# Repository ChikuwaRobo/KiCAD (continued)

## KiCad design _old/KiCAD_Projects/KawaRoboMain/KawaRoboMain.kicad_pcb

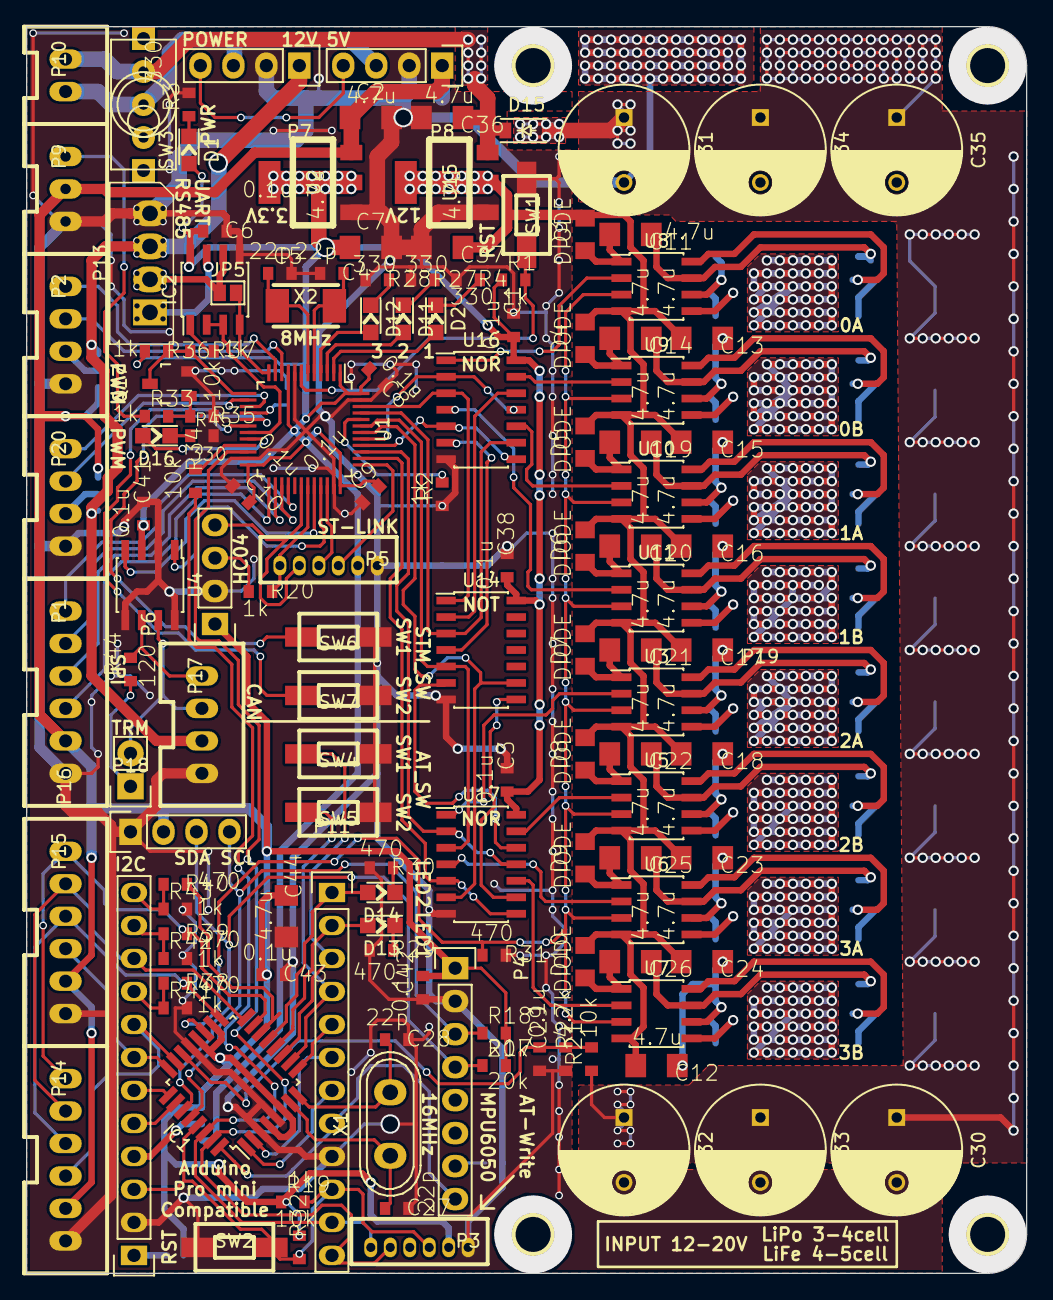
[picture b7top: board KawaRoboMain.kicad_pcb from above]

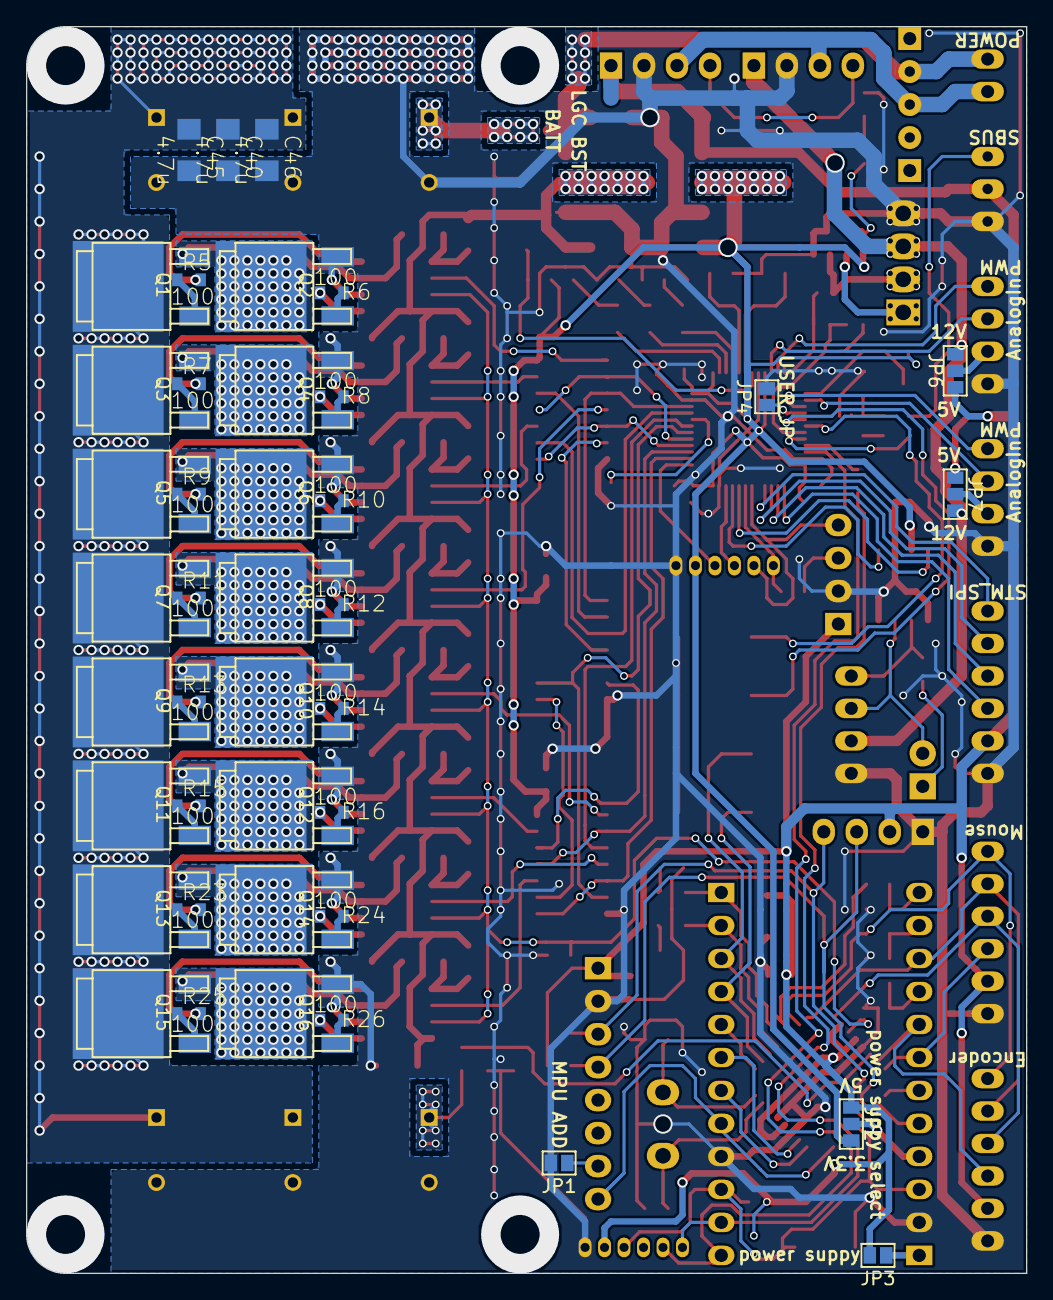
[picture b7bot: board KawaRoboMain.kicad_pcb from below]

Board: 2 copper layers, 77.0 x 96.0 mm, 178 parts (42 on the bottom side), 155 nets.

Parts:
C1, C3, C6, C8, C9, C10, C29, C38, C41, C42, C43: 0.1u; C1608_WP
C2, C7, C11, C12, C13, C14, C15, C16, C17, C18, C19, C20, C21, C22, C23, C24, C25, C26, C36, C37, C40, C44, C45, C46: 4.7u; C3216
C4, C5, C27, C28: 22p; C1608_WP
C30, C31, C32, C33, C34, C35: 220u; C_Radial_D10_L13_P5
D1, D2, D11, D12, D13, D14, D16: LED; LED_0805
D3, D4, D5, D6, D7, D8, D9, D10: DIODE; C2012
D15: DIODE; SOD-123
IC1: ATMEGA328P-A; TQFP-32_7x7mm_Pitch0.8mm
IC2: SP3485CN; SOIC-8_3.9x4.9mm_Pitch1.27mm
JP1, JP3, JP4, JP5: JUMPER; GS2
JP2, JP6, JP7: JUMPER3; GS3
P1, P14, P15: CONN_01X06; XA_6T
P2, P17, P20: CONN_01X04; XA_4T
P3, P5: CONN_01X06; ZH_6T
P4: CONN_01X08; Socket_Strip_Straight_1x08
P6, P7, P8, P18: CONN_01X04; Socket_Strip_Straight_1x04
P9: CONN_01X03; XA_3T
P10: CONN_01X02; XA_2T
P11, P12: CONN_01X12; Pin_Header_Straight_1x12
P13: CONN_01X04; Molex_SPOX-5267_22-03-5045_04x2.54mm_Straight
P16: CONN_01X02; Socket_Strip_Straight_1x02
P19: CONN_01X01; KawaRobo_Headsink
P21: CONN_01X01; kw
P22: CONN_01X01; ckw
Q1, Q2, Q3, Q4, Q5, Q6, Q7, Q8, Q9, Q10, Q11, Q12, Q13, Q14, Q15, Q16: MOSFET_N; SOT-428_GDS_compact
Q17: MOSFET_N; SOT-23_Handsoldering
R1, R2, R19, R20, R33, R36, R37, R41, R42, R43: 1k; C1608_WP
R3, R4, R27, R28, R45: 330; C1608_WP
R5, R6, R7, R8, R9, R10, R11, R12, R13, R14, R15, R16, R23, R24, R25, R26: 100; C1608_WP
R17, R18: 20k; C1608_WP
R21, R32, R34, R35: 10k; C1608_WP
R22: 4.7k; C1608_WP
R29, R30, R31, R38, R39, R40: 470; C1608_WP
R44: 120; C1608_WP
SW1, SW2, SW4, SW5, SW6, SW7: SW_PUSH; RP_SMD_Button
SW3: SWITCH_INV; SW_toggle_3P
U1: STM32F103_48; LQFP-48_7x7mm_Pitch0.5mm
U2: NCP1117ST33T3G; SOT-223_reg
U3, U5, U6, U7, U8, U9, U10, U11: NCP5359; SOIC-8_3.9x4.9mm_Pitch1.27mm
U4: MAX3051; SOIC-8_3.9x4.9mm_Pitch1.27mm
U14: 74HC04; SOIC-14_3.9x8.7mm_Pitch1.27mm
U15: NCP1117ST12T3G; SOT-223_reg
U16, U17: 74HC02; SOIC-14_3.9x8.7mm_Pitch1.27mm
X1: CRYSTAL; Crystal_HC50-U_Vertical
X2: CRYSTAL; ABM3_2pads

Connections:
+3.3V: C1.2, C3.2, C6.2, C7.1, C8.2, C9.2, C10.2, C38.2, C41.2, D1.1, IC2.8, JP2.3, P5.2, R1.1, R36.2, U1.1, U1.9, U1.24, U1.36, U1.48, U2.2, U4.3, U14.14, U16.14, U17.14
+5V: C2.1, C42.2, C43.2, C44.1, IC1.4, IC1.6, IC1.18, IC1.20, JP2.1, JP3.2, JP6.1, JP7.1, P1.2, P3.2, P4.1, P6.1, P8.1, P9.2, P14.2, P15.2, P18.2, R17.2, R18.2, R19.1, R32.1, U2.3
+12V: JP6.3, JP7.3, P7.1, P13.3, P17.2
+BATT: C30.1, C31.1, C32.1, C33.1, C34.1, C35.1, C40.1, C45.1, C46.1, D15.2, Q1.D, Q3.D, Q5.D, Q7.D, Q9.D, Q11.D, Q13.D, Q15.D, R21.1
/AT_A2: IC1.25, P12.6
/AT_A3: IC1.26, P12.5
/AT_LED1: D13.1, IC1.12, P11.2
/AT_LED2: D14.1, IC1.13, P11.1
/AT_RST: IC1.29, P3.3, P11.10, P12.3, R19.2, R32.2, SW2.2
/AT_RX: IC1.30, P3.6, P11.11, R34.2
/AT_SW1: IC1.11, P11.3, SW4.2
/AT_SW2: IC1.10, P11.4, SW5.2
/AT_TX: IC1.31, P3.5, P11.12, U1.22
/BOOT0: R2.2, U1.44
/CAN_RX: U1.32, U4.4
/CAN_TX: U1.33, U4.1
/DCDC_EN: P7.4, P8.4
/GD_12V: C12.2, C13.2, C15.2, C16.2, C17.2, C18.2, C23.2, C24.2, C37.1, D3.2, D4.2, D5.2, D6.2, D7.2, D8.2, D9.2, D10.2, U3.4, U5.4, U6.4, U7.4, U8.4, U9.4, U10.4, U11.4, U15.2
/I2C_SCL: IC1.28, P4.3, P18.4, R18.1
/I2C_SDA: IC1.27, P4.4, P18.3, R17.1
/INT0: IC1.32, P4.8, P11.8
/INT1: IC1.1, P11.7
/LOGIC_BATT: C36.1, D15.1, P10.2, SW3.1, U15.3
/Motor0CW: U1.41, U16.2, U16.11
/Motor0PWM: U1.46, U14.1, U16.3
/Motor1CW: U1.40, U16.5, U16.8
/Motor1PWM: U1.45, U14.3, U16.9
/Motor2CW: U1.39, U17.2, U17.11
/Motor2PWM: U1.43, U14.5, U17.3
/Motor3CW: U1.38, U17.5, U17.8
/Motor3PWM: U1.42, U14.9, U17.6
/Motor~SD: IC1.19, R31.2, U3.3, U5.3, U6.3, U7.3, U8.3, U9.3, U10.3, U11.3
/NRST: R1.2, SW1.2, U1.7
/OSC_IN: C4.1, U1.5, X2.1
/OSC_OUT: C5.1, U1.6, X2.2
/OUT_0_A: C11.1, Q1.S, Q2.D, U8.7
/OUT_0_B: C14.1, Q3.S, Q4.D, U9.7
/OUT_1_A: C19.1, Q5.S, Q6.D, U10.7
/OUT_1_B: C20.1, Q7.S, Q8.D, U11.7
/OUT_2_A: C21.1, Q9.S, Q10.D, U3.7
/OUT_2_B: C22.1, Q11.S, Q12.D, U5.7
/OUT_3_A: C25.1, Q13.S, Q14.D, U6.7
/OUT_3_B: C26.1, Q15.S, Q16.D, U7.7
/PWM_0_A: U8.2, U16.1
/PWM_0_B: U9.2, U16.13
/PWM_1_A: U10.2, U16.10
/PWM_1_B: U11.2, U16.4
/PWM_2_A: U3.2, U17.1
/PWM_2_B: U5.2, U17.13
/PWM_3_A: U6.2, U17.4
/PWM_3_B: U7.2, U17.10
/PWM_T2C1: P2.3, U1.10
/PWM_T2C2: P2.4, U1.11
/PWM_T3C1: P20.3, U1.14
/PWM_T3C2: P20.4, U1.15
/RAW: JP3.1, P12.1
/SBUS: P9.3, R33.1
/SERVO_DIR: IC2.2, IC2.3, U1.19
/SERVO_RX: Q17.D, R36.1, R37.2, U1.13
/SERVO_TX: IC2.4, JP5.2, U1.12
/SPI_MISO: IC1.16, P12.10, P14.5, P15.5
/SPI_MOSI: IC1.15, P14.6, P15.6, R39.1
/SPI_SCK: IC1.17, P14.4, P15.4, R38.1
/SPI_SS_ENC: IC1.23, P12.8, P14.3
/SPI_SS_Mouse: IC1.24, P12.7, P15.3
/SPI_SS_USB: IC1.14, R40.1
/STM_LED1: D2.1, U1.2
/STM_LED2: D11.1, U1.3
/STM_LED3: D12.1, U1.4
/STM_LED4: D16.1, U1.20
/STM_MISO: P1.5, U1.27
/STM_MOSI: P1.6, U1.28
/STM_SCK: P1.4, U1.26
/STM_SW1: SW6.2, U1.18
/STM_SW2: SW7.2, U1.17
/STM_~SS0: P1.3, U1.25
/SWCLK: P5.3, U1.37
/SWDIO: P5.4, U1.34
/USART_RX: P5.6, R20.1, U1.31
/USART_TX: P5.5, P6.4, U1.30
/VALVE_0: IC1.2, P11.6
/VALVE_1: IC1.9, P11.5
/batt_voltage: C29.1, IC1.22, R21.2, R22.1
GND: C1.1, C2.2, C3.1, C4.2, C5.2, C6.1, C7.2, C8.1, C9.1, C10.1, C12.1, C13.1, C15.1, C16.1, C17.1, C18.1, C23.1, C24.1, C27.1, C28.1, C29.2, C30.2, C31.2, C32.2, C33.2, C34.2, C35.2, C36.2, C37.2, C38.1, C40.2, C41.1, C42.1, C43.1, C44.2, C45.2, C46.2, IC1.3, IC1.5, IC1.21, IC2.5, JP1.2, JP4.2, P1.1, P2.1, P3.1, P4.2, P5.1, P6.2, P7.2, P8.2, P9.1, P11.9, P12.2, P13.4, P14.1, P15.1, P17.1, P18.1, P20.1, Q2.S, Q4.S, Q6.S, Q8.S, Q10.S, Q12.S, Q14.S, Q16.S, Q17.S, R2.1, R3.2, R4.2, R22.2, R27.2, R28.2, R29.2, R30.2, R31.1, R35.1, R41.2, R42.2, R43.2, R45.2, SW1.1, SW2.1, SW4.1, SW5.1, SW6.1, SW7.1, U1.8, U1.23, U1.35, U1.47, U2.1, U3.6, U4.2, U4.5, U4.8, U5.6, U6.6, U7.6, U8.6, U9.6, U10.6, U11.6, U14.7, U15.1, U16.7, U17.7
unnamed: C11.2, D3.1, U8.1
unnamed: C14.2, D4.1, U9.1
unnamed: C19.2, D5.1, U10.1
unnamed: C20.2, D6.1, U11.1
unnamed: C21.2, D7.1, U3.1
unnamed: C22.2, D8.1, U5.1
unnamed: C25.2, D9.1, U6.1
unnamed: C26.2, D10.1, U7.1
unnamed: C27.2, IC1.7, X1.1
unnamed: C28.2, IC1.8, X1.2
unnamed: D1.2, R3.1
unnamed: D2.2, R4.1
unnamed: D11.2, R27.1
unnamed: D12.2, R28.1
unnamed: D13.2, R29.1
unnamed: D14.2, R30.1
unnamed: D16.2, R45.1
unnamed: IC2.1, R37.1
unnamed: IC2.6, JP5.1, P13.2
unnamed: IC2.7, P13.1
unnamed: JP1.1, P4.7
unnamed: JP2.2, P12.4
unnamed: JP4.1, U1.16
unnamed: JP6.2, P2.2
unnamed: JP7.2, P20.2
unnamed: P6.3, R20.2
unnamed: P7.3, P8.3, P10.1, SW3.2
unnamed: P12.9, R38.2, R41.1
unnamed: P12.11, R39.2, R42.1
unnamed: P12.12, R40.2, R43.1
unnamed: P16.1, R44.1
unnamed: P16.2, P17.3, U4.7
unnamed: P17.4, R44.2, U4.6
unnamed: Q1.G, R5.1
unnamed: Q2.G, R6.1
unnamed: Q3.G, R7.1
unnamed: Q4.G, R8.1
unnamed: Q5.G, R9.1
unnamed: Q6.G, R10.1
unnamed: Q7.G, R11.1
unnamed: Q8.G, R12.1
unnamed: Q9.G, R13.1
unnamed: Q10.G, R14.1
unnamed: Q11.G, R15.1
unnamed: Q12.G, R16.1
unnamed: Q13.G, R23.1
unnamed: Q14.G, R24.1
unnamed: Q15.G, R25.1
unnamed: Q16.G, R26.1
unnamed: Q17.G, R33.2, R35.2
unnamed: R5.2, U8.8
unnamed: R6.2, U8.5
unnamed: R7.2, U9.8
unnamed: R8.2, U9.5
unnamed: R9.2, U10.8
unnamed: R10.2, U10.5
unnamed: R11.2, U11.8
unnamed: R12.2, U11.5
unnamed: R13.2, U3.8
unnamed: R14.2, U3.5
unnamed: R15.2, U5.8
unnamed: R16.2, U5.5
unnamed: R23.2, U6.8
unnamed: R24.2, U6.5
unnamed: R25.2, U7.8
unnamed: R26.2, U7.5
unnamed: R34.1, U1.21
unnamed: U14.2, U16.12
unnamed: U14.4, U16.6
unnamed: U14.6, U17.12
unnamed: U14.8, U17.9
